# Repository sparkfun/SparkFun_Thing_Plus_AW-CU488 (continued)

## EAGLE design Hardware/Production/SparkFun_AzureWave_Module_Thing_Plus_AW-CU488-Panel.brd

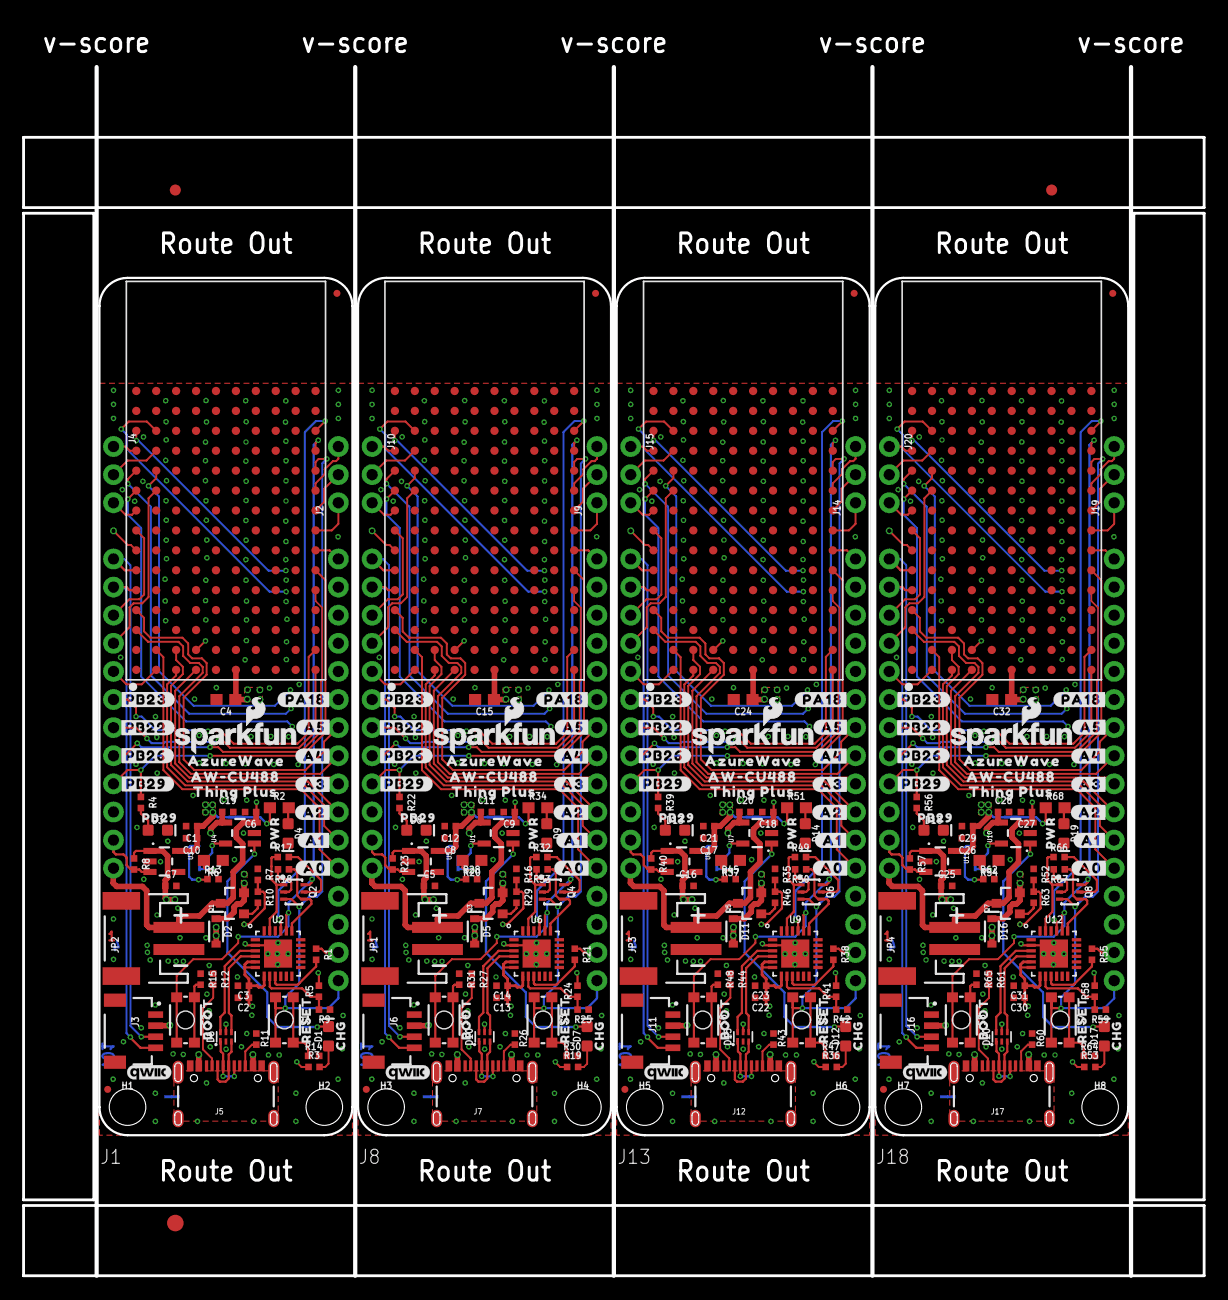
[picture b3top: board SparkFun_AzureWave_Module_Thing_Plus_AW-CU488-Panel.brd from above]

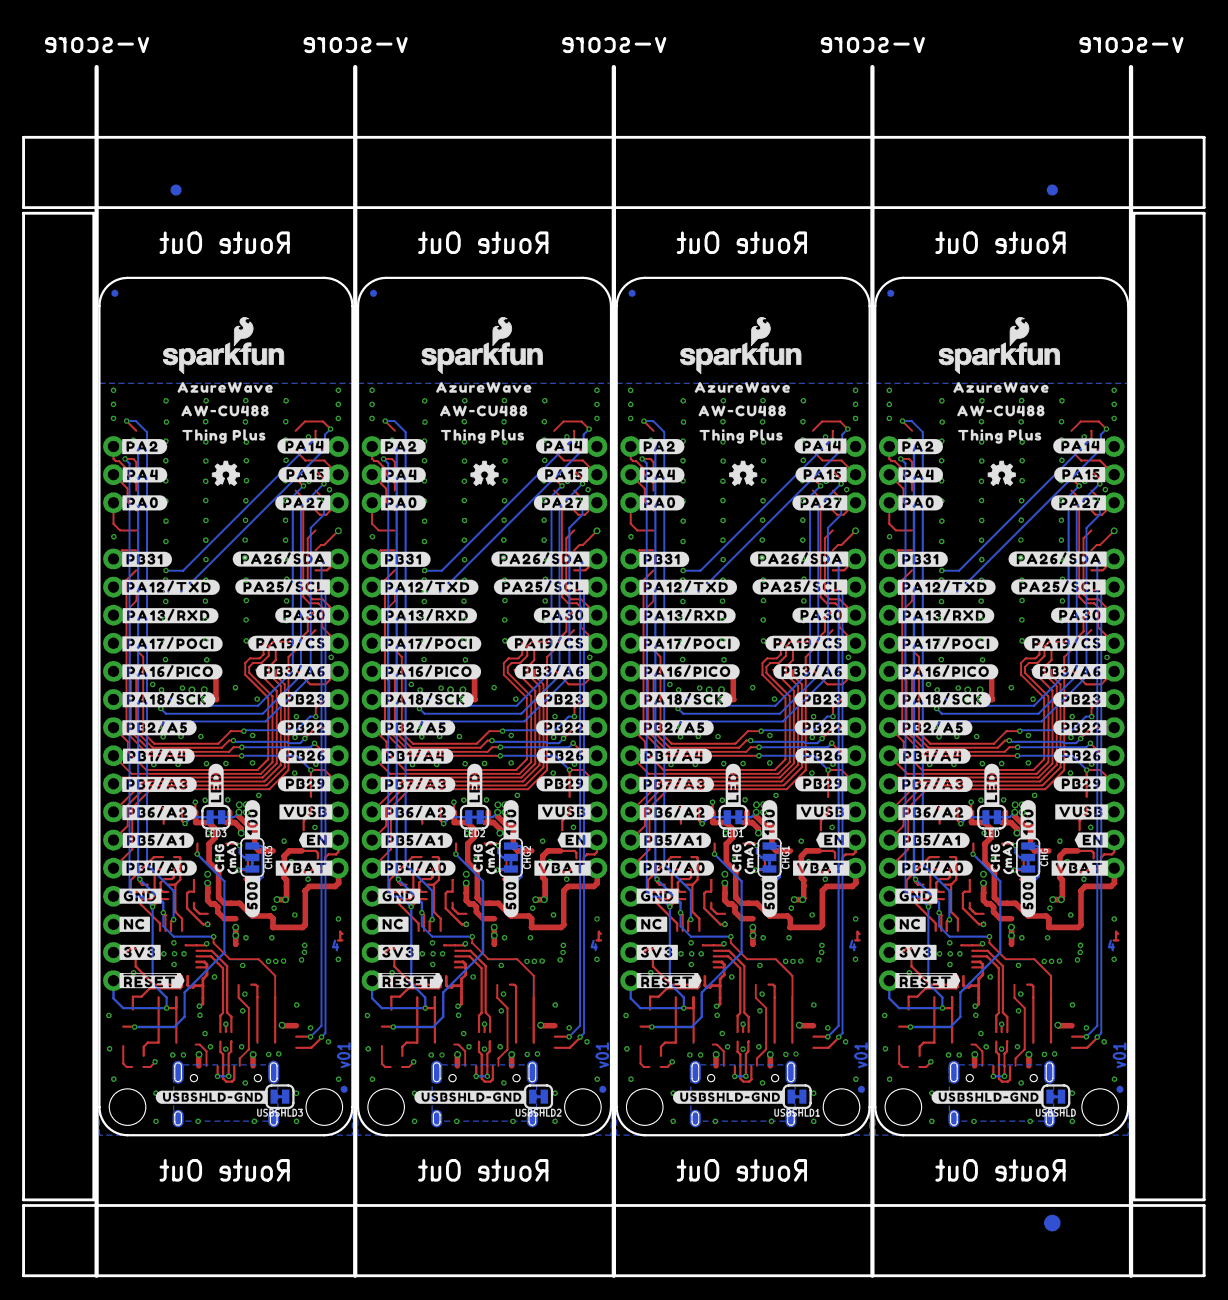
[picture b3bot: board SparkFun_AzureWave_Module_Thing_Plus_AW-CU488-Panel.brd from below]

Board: 4 copper layers, 106.7 x 109.2 mm, 494 parts (203 on the bottom side), 244 nets.

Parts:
C1, C12, C21, C29: 10uF; 0402-TIGHT
C2, C13, C22, C30: 0.1uF; 0402-TIGHT
C3, C6, C9, C11, C14, C18, C19, C20, C23, C27, C28, C31: 4.7uF; 0402-TIGHT
C4, C15, C24, C32: 10uF; 0603
C5, C7, C8, C10, C16, C17, C25, C26: 1.0uF; 0402-TIGHT
CHG, CHG1, CHG2, CHG3: SMT-JUMPER_3_1-NC_TRACE_SILK
D1, D7, D12, D17: Yellow; LED-0603
D2, D5, D11, D16: 1A/23V/620mV; SOD-323
D3, D8, D13, D18: BLUE; LED-0603
D4, D9, D14, D19: RED; LED-0603
D6, D10, D15, D20: PRTR5V0U2F; SOT886
E$1, E$2, E$3, E$4: FIDUCIAL-1X2
E$5, E$6: FIDUCIAL-1.5X3
FD1, FD2, FD3, FD4, FD5, FD6, FD7, FD8, FD9, FD10, FD11, FD12, FD13, FD14, FD15, FD16: FIDUCIALUFIDUCIAL; FIDUCIAL-MICRO
H1, H2, H3, H4, H5, H6, H7, H8: STAND-OFF
J1, J8, J13, J18: THING_PLUS
J2, J4, J9, J10, J14, J15, J19, J20: 1X03_NO_SILK
J3, J6, J11, J16: QWIIC_RA; JST04_1MM_RA
J5, J7, J12, J17: USB-C; USB-C-16P-4LAYER-ISOLATED
JP1, JP2, JP3, JP4: LiPo; JST-2-SMD
LED, LED1, LED2, LED3: SMT-JUMPER_2_NC_TRACE_SILK
LOGO1, LOGO2, LOGO11, LOGO16: OSHW-LOGOMINI; OSHW-LOGO-MINI
LOGO3, LOGO5, LOGO7, LOGO10, LOGO12, LOGO15, LOGO17, LOGO20: SFE_LOGO_NAME_FLAME.1_INCH; SFE_LOGO_NAME_FLAME_.1
LOGO4, LOGO8, LOGO13, LOGO18: FOUR_LAYER_WARNING
LOGO6, LOGO9, LOGO14, LOGO19: QWIIC_LOGO_4MM; QWIIC_4MM
Q1, Q3, Q5, Q7: 3.1A/30V/105mΩ; SOT23-3
Q2, Q4, Q6, Q8: MBT3904DW1T1; SC70-6
R1, R7, R13, R14, R16, R17, R18, R21, R28, R30, R32, R33, R35, R38, R45, R47, R49, R50, R52, R55, R62, R64, R66, R67: 10k; 0402-TIGHT
R2, R34, R51, R68: 4.7k; 0603
R3, R4, R15, R19, R22, R31, R36, R39, R48, R53, R56, R65: 1k; 0402-TIGHT
R5, R24, R41, R58: 22k; 0402-TIGHT
R6, R20, R37, R54: 2.0k; 0603
R8, R23, R40, R57: 100k; 0402-TIGHT
R9, R25, R42, R59: 33k; 0402-TIGHT
R10, R29, R46, R63: 100; 0402-TIGHT
R11, R12, R26, R27, R43, R44, R60, R61: 5.1k; 0402-TIGHT
S1, S3, S5, S7: SW1/RESET; TACTILE_SWITCH_SMD_4.6X2.8MM
S2, S4, S6, S8: SW2/BOOT; TACTILE_SWITCH_SMD_4.6X2.8MM
TP1, TP2, TP3, TP4: TP_15TH
U1, U4, U7, U10: MCP73831; SOT23-5
U2, U6, U9, U12: CP210X; QFN24
U3, U5, U8, U11: AP2112K-3.3V; SOT23-5
U$1, U$103, U$167, U$231: #PA13#RXD#19
U$2, U$81, U$145, U$209: BOOT0
U$3, U$49, U$73, U$78, U$130, U$139, U$194, U$203: CHG0
U$4, U$76, U$142, U$206: #500#0
U$5, U$104, U$168, U$232: #PA12#TXD#19
U$6, U$8, U$82, U$83, U$146, U$147, U$210, U$211: AZUREWAVE0
U$7, U$120, U$184, U$248: #PB29#0
U$9, U$27, U$80, U$84, U$144, U$148, U$208, U$212: AW#CU488_0
U$10, U$62, U$77, U$85, U$143, U$149, U$207, U$213: THING_PLUS_0
U$11, U$74, U$140, U$204: MA0
U$12, U$106, U$170, U$234: #PA0#32
U$13, U$86, U$150, U$214: AW-CU488; LGA150_AW-CU488
U$14, U$105, U$169, U$233: #PB31#19
U$15, U$121, U$185, U$249: #PB26#30
U$16, U$122, U$186, U$250: #PB22#30
U$17, U$123, U$187, U$251: #PB23#30
U$18, U$124, U$188, U$252: #A0#30
U$19, U$107, U$171, U$235: #PA4#32
U$20, U$125, U$189, U$253: #USBSHLD#GND#3
U$21, U$108, U$172, U$236: #PA2#32
U$22, U$109, U$173, U$237: #PA14#32
U$23, U$126, U$190, U$254: PWR0
U$24, U$110, U$174, U$238: #PA15#32
U$25, U$111, U$175, U$239: #PA26#SDA#32
U$26, U$112, U$176, U$240: #PA25#SCL#32
U$28, U$113, U$177, U$241: #PA30#32
U$29, U$127, U$191, U$255: #LED#0
U$30, U$128, U$192, U$256: #PB3#A6#0
U$31, U$114, U$178, U$242: #PA19#CS#32
U$32, U$69, U$135, U$199: #GND#0
U$33, U$115, U$179, U$243: #PA27#32
U$34, U$116, U$180, U$244: #PB23#32
U$35, U$87, U$151, U$215: PB290
U$36, U$117, U$181, U$245: #PB22#32
U$37, U$118, U$182, U$246: #PB26#32
U$38, U$119, U$183, U$247: #PB29#32
U$39, U$100, U$164, U$228: #PA18#SCK#19
U$40, U$101, U$165, U$229: #PA16#PICO#19
U$41, U$64, U$132, U$196: #VUSB#0
U$42, U$67, U$133, U$197: #VBAT#0
U$43, U$68, U$134, U$198: #EN#0
U$44, U$70, U$136, U$200: #NC#0
U$45, U$71, U$137, U$201: #3V3#0
U$46, U$72, U$138, U$202: ##RESET##0
U$47, U$102, U$166, U$230: #PA17#POCI#19
U$48, U$59, U$129, U$193: ORDERING_INSTRUCTIONS
U$50, U$79, U$131, U$195: RESET0
U$51, U$88, U$152, U$216: #PB4#A0#5
U$52, U$89, U$153, U$217: #PB5#A1#5
U$53, U$90, U$154, U$218: #A1#6
U$54, U$91, U$155, U$219: #A2#6
U$55, U$92, U$156, U$220: #A3#6
U$56, U$93, U$157, U$221: #A4#6
U$57, U$94, U$158, U$222: #A5#6
U$58, U$95, U$159, U$223: #PA18#6
U$60, U$75, U$141, U$205: #100#0
U$61, U$96, U$160, U$224: #PB6#A2#19
U$63, U$97, U$161, U$225: #PB7#A3#19
U$65, U$98, U$162, U$226: #PB1#A4#19
U$66, U$99, U$163, U$227: #PB2#A5#19
USBSHLD, USBSHLD1, USBSHLD2, USBSHLD3: SMT-JUMPER_2_NC_TRACE_SILK

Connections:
3.3V: C1.1, C2.1, C3.1, C4.1, C10.1, J1.27, J3.2, LED.1, R1.1, U2.5, U2.6, U2.7, U3.5, U$13.F1
3.3V1: C8.1, C12.1, C13.1, C14.1, C15.1, J6.2, J8.27, LED1.1, R21.1, U5.5, U6.5, U6.6, U6.7, U$86.F1
3.3V2: C17.1, C21.1, C22.1, C23.1, C24.1, J11.2, J13.27, LED2.1, R38.1, U8.5, U9.5, U9.6, U9.7, U$150.F1
3.3V3: C26.1, C29.1, C30.1, C31.1, C32.1, J16.2, J18.27, LED3.1, R55.1, U11.5, U12.5, U12.6, U12.7, U$214.F1
CC1: J5.A5, R12.2
CC2: J5.B5, R11.2
CC3: J7.B5, R26.2
CC4: J7.A5, R27.2
CC5: J12.B5, R43.2
CC6: J12.A5, R44.2
CC7: J17.B5, R60.2
CC8: J17.A5, R61.2
CHG: D1.C, U4.1
CHG1: D7.C, U1.1
CHG2: D12.C, U7.1
CHG3: D17.C, U10.1
CHIP_EN: J1.28, Q2.3, S1.1, S1.2, U$13.K11
CHIP_EN1: J8.28, Q4.3, S3.1, S3.2, U$86.K11
CHIP_EN2: J13.28, Q6.3, S5.1, S5.2, U$150.K11
CHIP_EN3: J18.28, Q8.3, S7.1, S7.2, U$214.K11
DTR: Q2.1, R17.1, U2.23
DTR1: Q4.1, R32.1, U6.23
DTR2: Q6.1, R49.1, U9.23
DTR3: Q8.1, R66.1, U12.23
EN: J1.11, R8.2, U3.3
EN1: J8.11, R23.2, U5.3
EN2: J13.11, R40.2, U8.3
EN3: J18.11, R57.2, U11.3
GND: C1.2, C2.2, C3.2, C4.2, C6.2, C7.2, C10.2, C19.2, D3.C, D4.C, D6.2, J1.25, J3.1, J5.GND, J5.GND2, JP2.1, R6.1, R7.1, R9.1, R11.1, R12.1, R13.2, R14.2, R15.1, U2.2, U2.PAD, U3.2, U4.2, U$13.A1, U$13.A2, U$13.A14, U$13.A15, U$13.B14, U$13.B15, U$13.C3, U$13.C4, U$13.C5, U$13.C6, U$13.C7, U$13.C8, U$13.C9, U$13.C10, U$13.C11, U$13.C12, U$13.C13, U$13.C14, U$13.C15, U$13.D3, U$13.D4, U$13.D5, U$13.D6, U$13.D7, U$13.D8, U$13.D9, U$13.D10, U$13.D11, U$13.D12, U$13.D13, U$13.D14, U$13.D15, U$13.E1, U$13.E2, U$13.E3, U$13.E4, U$13.E5, U$13.E6, U$13.E7, U$13.E8, U$13.E9, U$13.E10, U$13.E11, U$13.E12, U$13.E13, U$13.E14, U$13.E15, U$13.F2, U$13.F3, U$13.F4, U$13.F5, U$13.F6, U$13.F7, U$13.F8, U$13.F9, U$13.F10, U$13.F11, U$13.F12, U$13.F13, U$13.F14, U$13.F15, U$13.G1, U$13.G2, U$13.G3, U$13.G4, U$13.G5, U$13.G6, U$13.G7, U$13.G8, U$13.G9, U$13.G10, U$13.G11, U$13.G12, U$13.G13, U$13.G14, U$13.G15, U$13.H3, U$13.H4, U$13.H5, U$13.H6, U$13.H7, U$13.H8, U$13.H9, U$13.H10, U$13.H11, U$13.H12, U$13.H13, U$13.H14, U$13.H15, U$13.J14, U$13.J15, U$13.K3, U$13.K4, U$13.K14, U$13.K15, USBSHLD.1
GND1: C5.2, C8.2, C9.2, C11.2, C12.2, C13.2, C14.2, C15.2, D8.C, D9.C, D10.2, J6.1, J7.GND, J7.GND2, J8.25, JP1.1, R16.1, R20.1, R25.1, R26.1, R27.1, R28.2, R30.2, R31.1, U1.2, U5.2, U6.2, U6.PAD, U$86.A1, U$86.A2, U$86.A14, U$86.A15, U$86.B14, U$86.B15, U$86.C3, U$86.C4, U$86.C5, U$86.C6, U$86.C7, U$86.C8, U$86.C9, U$86.C10, U$86.C11, U$86.C12, U$86.C13, U$86.C14, U$86.C15, U$86.D3, U$86.D4, U$86.D5, U$86.D6, U$86.D7, U$86.D8, U$86.D9, U$86.D10, U$86.D11, U$86.D12, U$86.D13, U$86.D14, U$86.D15, U$86.E1, U$86.E2, U$86.E3, U$86.E4, U$86.E5, U$86.E6, U$86.E7, U$86.E8, U$86.E9, U$86.E10, U$86.E11, U$86.E12, U$86.E13, U$86.E14, U$86.E15, U$86.F2, U$86.F3, U$86.F4, U$86.F5, U$86.F6, U$86.F7, U$86.F8, U$86.F9, U$86.F10, U$86.F11, U$86.F12, U$86.F13, U$86.F14, U$86.F15, U$86.G1, U$86.G2, U$86.G3, U$86.G4, U$86.G5, U$86.G6, U$86.G7, U$86.G8, U$86.G9, U$86.G10, U$86.G11, U$86.G12, U$86.G13, U$86.G14, U$86.G15, U$86.H3, U$86.H4, U$86.H5, U$86.H6, U$86.H7, U$86.H8, U$86.H9, U$86.H10, U$86.H11, U$86.H12, U$86.H13, U$86.H14, U$86.H15, U$86.J14, U$86.J15, U$86.K3, U$86.K4, U$86.K14, U$86.K15, USBSHLD1.1
GND2: C16.2, C17.2, C18.2, C20.2, C21.2, C22.2, C23.2, C24.2, D13.C, D14.C, D15.2, J11.1, J12.GND, J12.GND2, J13.25, JP3.1, R35.1, R37.1, R42.1, R43.1, R44.1, R45.2, R47.2, R48.1, U7.2, U8.2, U9.2, U9.PAD, U$150.A1, U$150.A2, U$150.A14, U$150.A15, U$150.B14, U$150.B15, U$150.C3, U$150.C4, U$150.C5, U$150.C6, U$150.C7, U$150.C8, U$150.C9, U$150.C10, U$150.C11, U$150.C12, U$150.C13, U$150.C14, U$150.C15, U$150.D3, U$150.D4, U$150.D5, U$150.D6, U$150.D7, U$150.D8, U$150.D9, U$150.D10, U$150.D11, U$150.D12, U$150.D13, U$150.D14, U$150.D15, U$150.E1, U$150.E2, U$150.E3, U$150.E4, U$150.E5, U$150.E6, U$150.E7, U$150.E8, U$150.E9, U$150.E10, U$150.E11, U$150.E12, U$150.E13, U$150.E14, U$150.E15, U$150.F2, U$150.F3, U$150.F4, U$150.F5, U$150.F6, U$150.F7, U$150.F8, U$150.F9, U$150.F10, U$150.F11, U$150.F12, U$150.F13, U$150.F14, U$150.F15, U$150.G1, U$150.G2, U$150.G3, U$150.G4, U$150.G5, U$150.G6, U$150.G7, U$150.G8, U$150.G9, U$150.G10, U$150.G11, U$150.G12, U$150.G13, U$150.G14, U$150.G15, U$150.H3, U$150.H4, U$150.H5, U$150.H6, U$150.H7, U$150.H8, U$150.H9, U$150.H10, U$150.H11, U$150.H12, U$150.H13, U$150.H14, U$150.H15, U$150.J14, U$150.J15, U$150.K3, U$150.K4, U$150.K14, U$150.K15, USBSHLD2.1
GND3: C25.2, C26.2, C27.2, C28.2, C29.2, C30.2, C31.2, C32.2, D18.C, D19.C, D20.2, J16.1, J17.GND, J17.GND2, J18.25, JP4.1, R52.1, R54.1, R59.1, R60.1, R61.1, R62.2, R64.2, R65.1, U10.2, U11.2, U12.2, U12.PAD, U$214.A1, U$214.A2, U$214.A14, U$214.A15, U$214.B14, U$214.B15, U$214.C3, U$214.C4, U$214.C5, U$214.C6, U$214.C7, U$214.C8, U$214.C9, U$214.C10, U$214.C11, U$214.C12, U$214.C13, U$214.C14, U$214.C15, U$214.D3, U$214.D4, U$214.D5, U$214.D6, U$214.D7, U$214.D8, U$214.D9, U$214.D10, U$214.D11, U$214.D12, U$214.D13, U$214.D14, U$214.D15, U$214.E1, U$214.E2, U$214.E3, U$214.E4, U$214.E5, U$214.E6, U$214.E7, U$214.E8, U$214.E9, U$214.E10, U$214.E11, U$214.E12, U$214.E13, U$214.E14, U$214.E15, U$214.F2, U$214.F3, U$214.F4, U$214.F5, U$214.F6, U$214.F7, U$214.F8, U$214.F9, U$214.F10, U$214.F11, U$214.F12, U$214.F13, U$214.F14, U$214.F15, U$214.G1, U$214.G2, U$214.G3, U$214.G4, U$214.G5, U$214.G6, U$214.G7, U$214.G8, U$214.G9, U$214.G10, U$214.G11, U$214.G12, U$214.G13, U$214.G14, U$214.G15, U$214.H3, U$214.H4, U$214.H5, U$214.H6, U$214.H7, U$214.H8, U$214.H9, U$214.H10, U$214.H11, U$214.H12, U$214.H13, U$214.H14, U$214.H15, U$214.J14, U$214.J15, U$214.K3, U$214.K4, U$214.K14, U$214.K15, USBSHLD3.1
LP_UART_RXD: J1.15, U$13.B13
LP_UART_RXD1: J8.15, U$86.B13
LP_UART_RXD2: J13.15, U$150.B13
LP_UART_RXD3: J18.15, U$214.B13
LP_UART_TXD: J1.14, U$13.A13
LP_UART_TXD1: J8.14, U$86.A13
LP_UART_TXD2: J13.14, U$150.A13
LP_UART_TXD3: J18.14, U$214.A13
unnamed: R1.2, U2.9
unnamed: D3.A, R4.2
unnamed: Q2.5, R17.2
unnamed: R5.1, R9.2, U2.8
unnamed: Q2.2, R18.2
unnamed: D7.A, R19.2
unnamed: Q1.1, R10.2
unnamed: R15.2, S2.3, S2.4
unnamed: CHG.2, U4.5
unnamed: R14.1, S1.3, S1.4
unnamed: CHG.1, R13.1
unnamed: LED.2, R2.1
unnamed: CHG.3, R6.2
unnamed: D4.A, R2.2
unnamed: D6.6, U2.3
unnamed: D6.1, J5.A6, J5.B6
unnamed: D1.A, R3.2
unnamed: D6.4, U2.4
unnamed: D6.3, J5.A7, J5.B7
unnamed: R21.2, U6.9
unnamed: D8.A, R22.2
unnamed: R24.1, R25.2, U6.8
unnamed: CHG1.2, U1.5
unnamed: CHG1.1, R28.1
unnamed: CHG1.3, R20.2
unnamed: Q3.1, R29.2
unnamed: R30.1, S3.3, S3.4
unnamed: R31.2, S4.3, S4.4
unnamed: Q4.5, R32.2
unnamed: Q4.2, R33.2
unnamed: LED1.2, R34.1
unnamed: D9.A, R34.2
unnamed: D10.6, U6.3
unnamed: D10.1, J7.A6, J7.B6
unnamed: D10.4, U6.4
unnamed: D10.3, J7.A7, J7.B7
unnamed: D12.A, R36.2
unnamed: R38.2, U9.9
unnamed: D13.A, R39.2
unnamed: R41.1, R42.2, U9.8
unnamed: CHG2.2, U7.5
unnamed: CHG2.1, R45.1
unnamed: CHG2.3, R37.2
unnamed: Q5.1, R46.2
unnamed: R47.1, S5.3, S5.4
unnamed: R48.2, S6.3, S6.4
unnamed: Q6.5, R49.2
unnamed: Q6.2, R50.2
unnamed: LED2.2, R51.1
unnamed: D14.A, R51.2
unnamed: D15.6, U9.3
unnamed: D15.1, J12.A6, J12.B6
unnamed: D15.4, U9.4
unnamed: D15.3, J12.A7, J12.B7
unnamed: D17.A, R53.2
unnamed: R55.2, U12.9
unnamed: D18.A, R56.2
unnamed: R58.1, R59.2, U12.8
unnamed: CHG3.2, U10.5
unnamed: CHG3.1, R62.1
unnamed: CHG3.3, R54.2
unnamed: Q7.1, R63.2
unnamed: R64.1, S7.3, S7.4
unnamed: R65.2, S8.3, S8.4
unnamed: Q8.5, R66.2
unnamed: Q8.2, R67.2
unnamed: LED3.2, R68.1
unnamed: D19.A, R68.2
unnamed: D20.6, U12.3
unnamed: D20.1, J17.A6, J17.B6
unnamed: D20.4, U12.4
unnamed: D20.3, J17.A7, J17.B7
PA0: J2.1, U$13.K8
PA1: J10.3, U$86.A9
PA2: J2.3, U$13.K10
PA3: J8.3, U$86.A8
PA4: J2.2, U$13.K9
PA5: J9.3, U$86.K10
PA6: J9.1, U$86.K8
PA7: J9.2, U$86.K9
PA7/UART-LOG-TXD: Q2.6, S2.1, S2.2, U2.20, U$13.K12
PA7/UART-LOG-TXD1: Q4.6, S4.1, S4.2, U6.20, U$86.K12
PA7/UART-LOG-TXD2: Q6.6, S6.1, S6.2, U9.20, U$150.K12
PA7/UART-LOG-TXD3: Q8.6, S8.1, S8.2, U12.20, U$214.K12
PA8: J10.1, U$86.A12
PA8/UART-LOG-RXD: U2.21, U$13.K13
PA8/UART-LOG-RXD1: U6.21, U$86.K13
PA8/UART-LOG-RXD2: U9.21, U$150.K13
PA8/UART-LOG-RXD3: U12.21, U$214.K13
PA9: J10.2, U$86.B12
PA10: TP2.1, U$86.A7
PA11: J15.3, U$150.A9
PA12: J13.3, U$150.A8
PA13: J14.3, U$150.K10
PA14: J4.1, U$13.A12
PA15: J4.2, U$13.B12
PA16: J14.1, U$150.K8
PA16/PICO: J1.17, U$13.A11
PA16/PICO1: J8.17, U$86.A11
PA16/PICO2: J13.17, U$150.A11
PA16/PICO3: J18.17, U$214.A11
PA17: J14.2, U$150.K9
PA17/POCI: J1.16, U$13.B11
PA17/POCI1: J8.16, U$86.B11
PA17/POCI2: J13.16, U$150.B11
PA17/POCI3: J18.16, U$214.B11
PA18: J15.1, U$150.A12
PA18/SCK: J1.18, U$13.A10
PA18/SCK1: J8.18, U$86.A10
PA18/SCK2: J13.18, U$150.A10
PA18/SCK3: J18.18, U$214.A10
PA19: J15.2, U$150.B12
PA19/CS: J1.4, U$13.B10
PA19/CS1: J8.4, U$86.B10
PA19/CS2: J13.4, U$150.B10
PA19/CS3: J18.4, U$214.B10
PA20: TP3.1, U$150.A7
PA21: J20.3, U$214.A9
PA22: J18.3, U$214.A8
PA23: J19.3, U$214.K10
PA24: J19.1, U$214.K8
PA25: J19.2, U$214.K9
PA25/SCL: J1.2, J3.4, U$13.A5
PA25/SCL1: J6.4, J8.2, U$86.A5
PA25/SCL2: J11.4, J13.2, U$150.A5
PA25/SCL3: J16.4, J18.2, U$214.A5
PA26: J20.1, U$214.A12
PA26/SDA: J1.1, J3.3, U$13.A6
PA26/SDA1: J6.3, J8.1, U$86.A6
PA26/SDA2: J11.3, J13.1, U$150.A6
PA26/SDA3: J16.3, J18.1, U$214.A6
PA27: J4.3, U$13.A9
PA28: TP1.1, U$13.A7
PA29: J20.2, U$214.B12
PA30: J1.3, U$13.A8
PA31: TP4.1, U$214.A7
PB1: J8.7, U$86.K1
PB1/A1: J8.20, U$86.A3
PB1/A2: J13.20, U$150.A3
PB1/A3: J18.20, U$214.A3
PB1/A4: J1.20, U$13.A3
PB2: J8.6, U$86.K2
PB2/A1: J8.19, U$86.A4
PB2/A2: J13.19, U$150.A4
PB2/A3: J18.19, U$214.A4
PB2/A5: J1.19, U$13.A4
PB3: J8.8, U$86.K5
PB3/A1: J8.5, U$86.B1
PB3/A2: J13.5, U$150.B1
PB3/A3: J18.5, U$214.B1
PB3/A6: J1.5, U$13.B1
PB4: J8.9, R22.1, U$86.K6
PB4/A0: J1.24, U$13.B2
PB4/A1: J8.24, U$86.B2
PB4/A2: J13.24, U$150.B2
PB4/A3: J18.24, U$214.B2
PB5: J8.13, U$86.K7
PB5/A1: J1.23, U$13.C1
PB5/A2: J8.23, U$86.C1
PB5/A3: J13.23, U$150.C1
PB5/A4: J18.23, U$214.C1
PB6: J13.7, U$150.K1
PB6/A1: J8.22, U$86.C2
PB6/A2: J1.22, U$13.C2
PB6/A3: J13.22, U$150.C2
PB6/A4: J18.22, U$214.C2
PB7: J13.6, U$150.K2
PB7/A1: J8.21, U$86.D1
PB7/A2: J13.21, U$150.D1
PB7/A3: J1.21, U$13.D1
PB7/A4: J18.21, U$214.D1
PB8: J13.8, U$150.K5
PB9: J13.9, R39.1, U$150.K6
PB10: J13.13, U$150.K7
PB11: J18.7, U$214.K1
PB12: J18.6, U$214.K2
PB13: J18.8, U$214.K5
PB14: J18.9, R56.1, U$214.K6
PB15: J18.13, U$214.K7
PB22: J1.7, U$13.K1
PB23: J1.6, U$13.K2
PB26: J1.8, U$13.K5
PB29: J1.9, R4.1, U$13.K6
PB31: J1.13, U$13.K7
RTS: Q2.4, R18.1, U2.19
RTS1: Q4.4, R33.1, U6.19
RTS2: Q6.4, R50.1, U9.19
RTS3: Q8.4, R67.1, U12.19
USB_SHLD: J5.SHLD1, J5.SHLD2, J5.SHLD3, J5.SHLD4, J5.SHLD5, J5.SHLD6, J5.SHLD7, J5.SHLD8, USBSHLD.2
USB_SHLD1: J7.SHLD1, J7.SHLD2, J7.SHLD3, J7.SHLD4, J7.SHLD5, J7.SHLD6, J7.SHLD7, J7.SHLD8, USBSHLD1.2
USB_SHLD2: J12.SHLD1, J12.SHLD2, J12.SHLD3, J12.SHLD4, J12.SHLD5, J12.SHLD6, J12.SHLD7, J12.SHLD8, USBSHLD2.2
USB_SHLD3: J17.SHLD1, J17.SHLD2, J17.SHLD3, J17.SHLD4, J17.SHLD5, J17.SHLD6, J17.SHLD7, J17.SHLD8, USBSHLD3.2
VIN: C7.1, D2.C, Q1.2, R8.1, U3.1
VIN1: C5.1, D5.C, Q3.2, R23.1, U5.1
VIN2: C16.1, D11.C, Q5.2, R40.1, U8.1
VIN3: C25.1, D16.C, Q7.2, R57.1, U11.1
V_BATT: C6.1, J1.12, JP2.2, Q1.3, U4.3, U$13.D2
V_BATT1: C9.1, J8.12, JP1.2, Q3.3, U1.3, U$86.D2
V_BATT2: C18.1, J13.12, JP3.2, Q5.3, U7.3, U$150.D2
V_BATT3: C27.1, J18.12, JP4.2, Q7.3, U10.3, U$214.D2
V_USB: C19.1, D2.A, D6.5, J1.10, J5.VBUS1, J5.VBUS2, R3.1, R5.2, R7.2, R10.1, U4.4
V_USB1: C11.1, D5.A, D10.5, J7.VBUS1, J7.VBUS2, J8.10, R16.2, R19.1, R24.2, R29.1, U1.4
V_USB2: C20.1, D11.A, D15.5, J12.VBUS1, J12.VBUS2, J13.10, R35.2, R36.1, R41.2, R46.1, U7.4
V_USB3: C28.1, D16.A, D20.5, J17.VBUS1, J17.VBUS2, J18.10, R52.2, R53.1, R58.2, R63.1, U10.4

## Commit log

2022-02-25 Module device created in temp library
2022-03-30 layout starting - bare minimum
2022-03-30 vbat meas connection and some net cleanup
2022-04-11 layout almost there
2022-04-12 Layout done for proto v01
2022-05-03 tweaking for pin functions in progress
2022-05-04 Routed but needs cleanup and silk updates
    -added auto-reset back in
    -broke out extra GPIO to "bonus" PTH headers on upper sides
2022-05-04 More Layout work - pretty much 99% done
2022-05-05 pre-design review notes and fixes
    -power symbols, Q1, U3, U4 updated to latest libraries
    -consolidated all low current signals to 10mils vias. V_USB (x4), 3.3V (x3), VIN (x2) are still 15mil for higher current capabilities.
    -Center anchor for section text in sch
    -added via near transitioning digital signals near PB26/PB28 PTH headers
    -moved R15 about 20mil to the right to give more room for rework/give more room for the JST connector
    -reduced paste on modules pads by 2mils on either side (for a reduction total on the diameter of the paste hole of 4 mils).
2022-05-05 added USB Shield GND jumper
    -added "shield" net polygons (and via) to connect all 8 shield pads. And add a little extra strength.
    -added jumper to connect USB-C shield to GND (normally closed via trace).
    -moved OSHW logo and version text.
2022-05-06 group review mods
    -add power LED and jumper
    -fixed "connected" typo in sch
    -add ESD protection on D+/D- lines
    -added more vias for power lines (every part of the stream from VUSB to 3.3V to the module).
    -added GND vias under module
    -broke out PB3/A6/SWD_CLK to extra upper side PTH header
2022-05-06 Module prod ID
2022-05-06 made symbol pin name for download active low
2022-05-06 final check finds
    -Scooted VIN trace for GND flow near Vreg
    -nudged trace off of PA27 to avoid acid trap
    -updated pin names to include SWD functions in symbol
2022-05-06 prototype panel production files (brd and gerbers)
2022-05-19 Re-routed traces off of charge current select jumper
    -The traces were unnecessarily tight off the jumpers and easy to cut on accident. Now they have more clearance.
    -Also bumped version to v10 in brd and sch
2022-06-13 changes found during proto testing
    -removed R14 pulldown on reset button. It now pulls down directly to GND when pressed.
    -adjusted Charge LED resistor to lower brightness (R3 changed from 1K to 4.7K)
    -Added PTH header breakouts for UART LOG RX and TX.
    -Changed silk on all pins to more user-friendly/common digital numbers.
    -Added jumpers to more easily remove auto-boot circuit if needed for advanced use cases
2022-06-13 centered SFE logo and product name text
2022-06-14 Reds review catches
    -added note in SCH about pwr LED jumper
    -approved jumper overlap DRC errors
    -added table lines to schematic info about auto-reset
    -moved OSHW logo over via
    -removed unncessary GND vias under USB-C
2022-06-14 more changes from reds review
    -auto-reset disable jumpers changed to JP1 and JP2
    -added more measures to top pht header on header rows
    -swapped vreg from ap2112 to XC6222
    -Add SFE LOGO to bottom silk
    -more gnd vias near potential gnd loops
    -fixed acid traps
2022-06-14 AW-CU488 library work
    -removed NC pin
    -took "$" out of part name attribute
2022-06-14 RED power LED limiting resistor reduced to 1K for better brightness matching
2022-06-15 Blue LED resistor (R4) corrected to 4.7K
    also updated Prod_ID on xc6222 vreg
2022-06-16 Production Panel BRD and Gerbers v10
2022-06-29 added arduino pin mapping table to schematic
2022-07-13 Added SPI1 pin-names to device symbol in schematic
2022-07-13 audio codec specific pin-names into sch symbol
2022-07-28 Dimensional drawings and schematic PDF
2022-07-28 correcting sch PDF filename
2022-08-22 Updated datasheet for AW-CU488 module
